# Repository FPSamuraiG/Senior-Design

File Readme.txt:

An Electronic Enrichment System for Saltwater Animal Enclosures

University of Cincinnati
CEAS
EE/ELTN Senior Design
April 2022

Team Members:
  Chris Dombrosky
  Brandon Carroll
  Nathaniel Collum
  Hayden Lampert

Advisors:
  Dr. Dieter Vanderelst
  Dr. Katie Kalafut
  
This repository contains code, PCB files, 3D models, and documentation for this senior design project.

3D Models: Contains 3D models for the project's pushbutton enclosure and wireless charging pad as .step files. Also contains .stl files for 3D printing these components.

Datasheets: Contains manufacturer datasheets for key project components.

PDB Files: Contains EAGLE files for the projects PCBs. Also contains an EAGLE library for custom components used on the PCBs, zipped gerber files for manufacturing additional copies, and component lists for the PCBs.

Release: Contains the .hex file for programming the microcontroller used in this project.

Senior_Design.X: MPLAB X IDE project folder for the microcontroller code. Can be opened as a project in MPLAB X IDE with MPLAB Code Configurator installed.

Project Abstract:

In this project, we designed a prototype input collection system for use in interactive electronic systems in saltwater animal enclosures. Increasing interactivity in enclosures has the potential to improve animal welfare and allow for research and behavior monitoring. Implementing an input device underwater is made difficult by the lack of premade input devices that function underwater, waterproofing requirements, and the ineffectiveness of wireless communication methods underwater. To address these challenges, we designed a prototype input system that includes a custom submersible pushbutton, fiber optic communication, wirelessly rechargeable battery, and extensive waterproofing features. This prototype functions as a pushbutton that can be installed underwater and connected to an Arduino through a fiber optic cable. It provides a tactile input for animals while maintaining safety by not exposing wires or electronics to water. Although it only functions as a pushbutton in its current state, this prototype was designed to be easy to use and easy to add additional sensors or input devices to. Overall, it meets the basic needs presented by our advisors while also making future work and improvements easier.

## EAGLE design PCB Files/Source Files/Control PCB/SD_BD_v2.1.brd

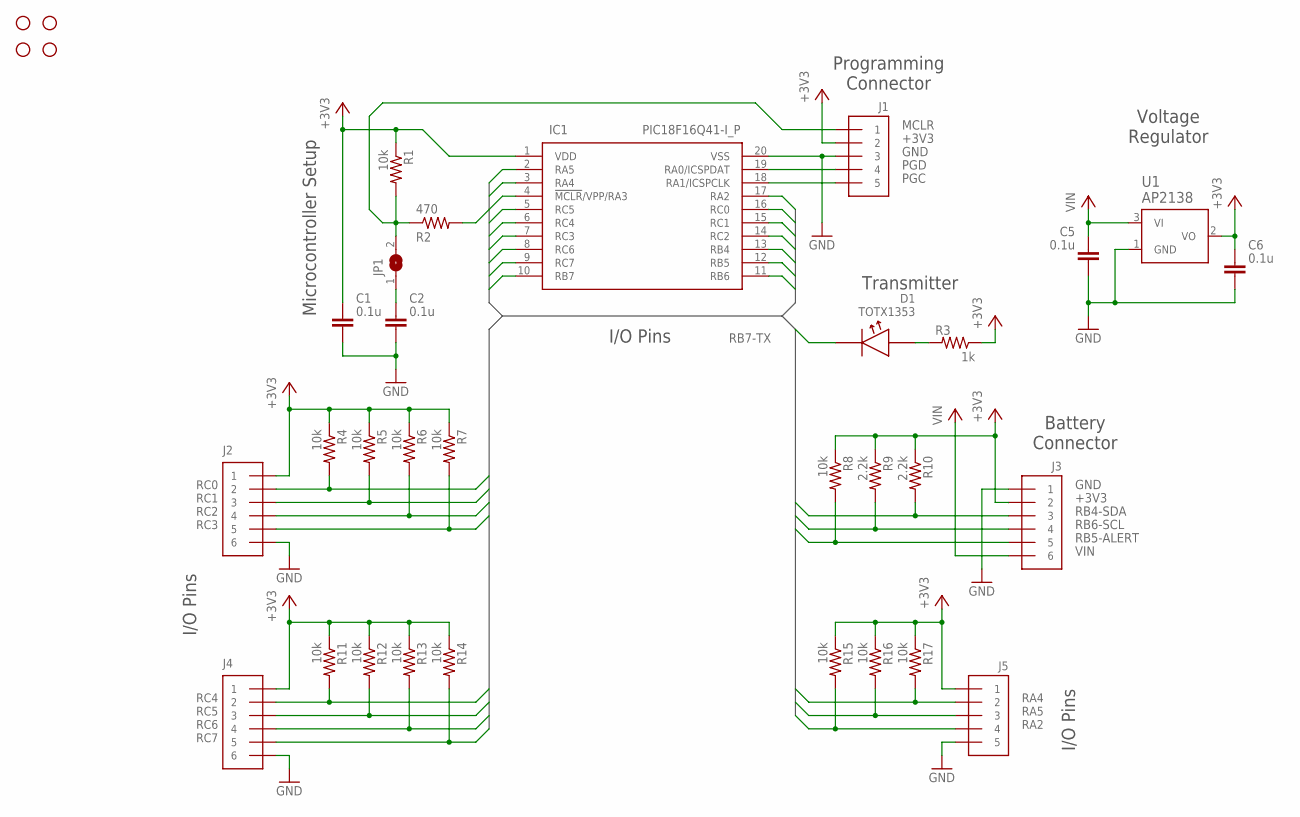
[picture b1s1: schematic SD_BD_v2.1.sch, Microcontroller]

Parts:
C1, C2, C5, C6: 0.1u; CAPC3216X135
D1: TOTX1353; TOXX1353
H1, H2, H3, H4: STAND-OFF
IC1: PIC18F16Q41-I_P; DIP794W56P254L2591H533Q20N
J1: M20-9990546; HDR-5-M
J2, J3, J4: PPTC061LFBN-RC; HDR-6-F
J5: PPTC051LFBN-RC; HDR-5-F
JP1: SJ
R1, R4, R5, R6, R7, R8, R11, R12, R13, R14, R15, R16, R17: 10k; R1206
R2: 470; R1206
R3: 1k; R1206
R9, R10: 2.2k; R1206
U1: AP2138N-3.3TRG1IC3_AP2138N-3.3TRG1_DIO-M; IC3_AP2138N-3.3TRG1_DIO-M

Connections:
+3V3: C1.1, C6.1, IC1.1 (VDD), J1.2, J2.1, J3.2, J4.1, J5.1, R1.1, R3.1, R4.1, R5.1, R6.1, R7.1, R8.1, R9.1, R10.1, R11.1, R12.1, R13.1, R14.1, R15.1, R16.1, R17.1, U1.2 (VO)
GND: C1.2, C2.2, C5.2, C6.2, IC1.20 (VSS), J1.3, J2.6, J3.1, J4.6, J5.5, U1.1 (GND)
MCLR: J1.1, JP1.2, R1.2, R2.1
unnamed: D1.3 (A), R3.2
unnamed: IC1.4 (!MCLR!/VPP/RA3), R2.2
unnamed: C2.1, JP1.1
PGC: IC1.18 (RA1/ICSPCLK), J1.5
PGD: IC1.19 (RA0/ICSPDAT), J1.4
RA2: IC1.17 (RA2), J5.4, R15.2
RA4: IC1.3 (RA4), J5.2, R17.2
RA5: IC1.2 (RA5), J5.3, R16.2
RB4-SDA: IC1.13 (RB4), J3.3, R10.2
RB5-ALERT: IC1.12 (RB5), J3.5, R8.2
RB6-SCL: IC1.11 (RB6), J3.4, R9.2
RB7-TX: D1.2 (K), IC1.10 (RB7)
RC0: IC1.16 (RC0), J2.2, R4.2
RC1: IC1.15 (RC1), J2.3, R5.2
RC2: IC1.14 (RC2), J2.4, R6.2
RC3: IC1.7 (RC3), J2.5, R7.2
RC4: IC1.6 (RC4), J4.2, R11.2
RC5: IC1.5 (RC5), J4.3, R12.2
RC6: IC1.8 (RC6), J4.4, R13.2
RC7: IC1.9 (RC7), J4.5, R14.2
VIN: C5.1, J3.6, U1.3 (VI)

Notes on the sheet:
I/O Pins
Transmitter
Microcontroller Setup
Voltage Regulator
Programming Connector
Battery Connector

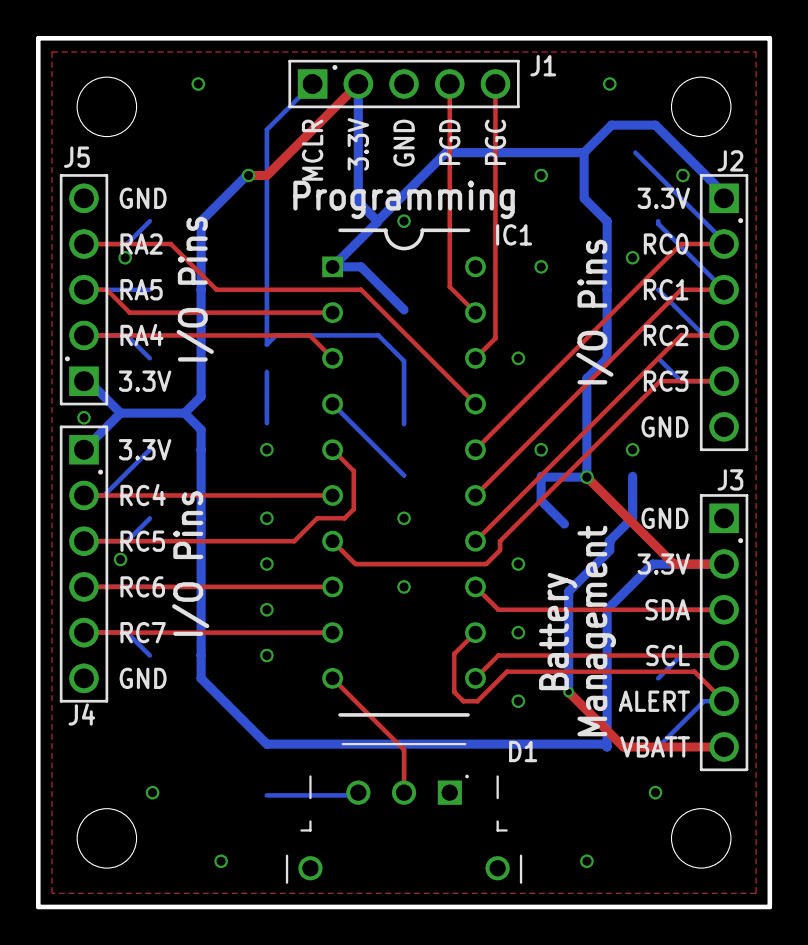
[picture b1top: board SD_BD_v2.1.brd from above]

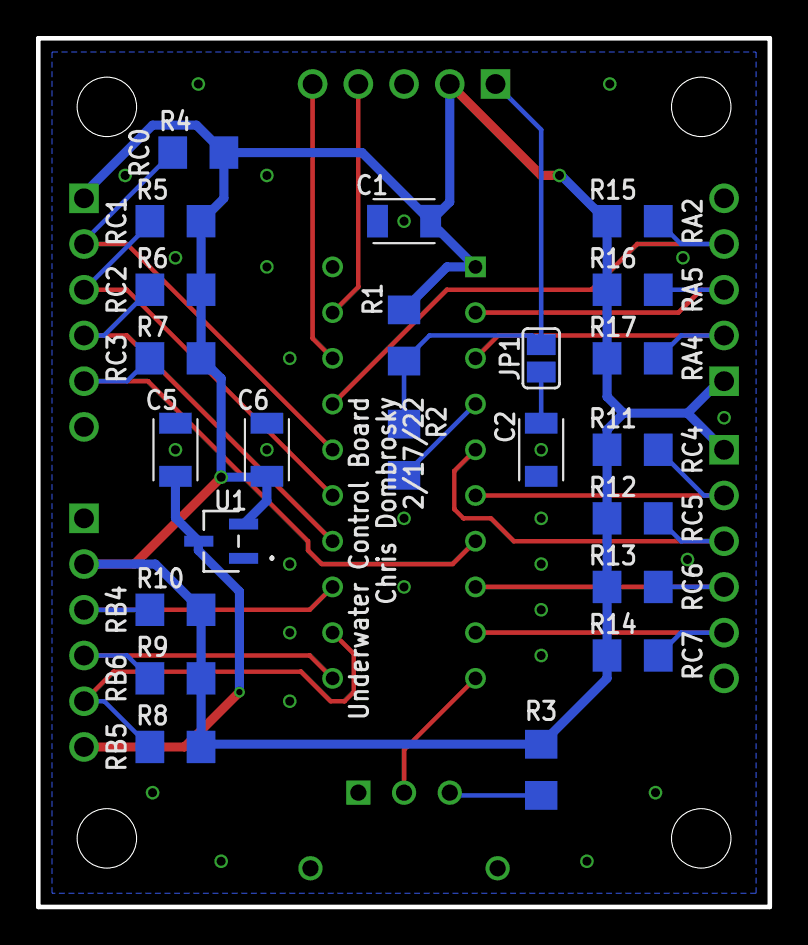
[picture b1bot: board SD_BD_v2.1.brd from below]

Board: 2 copper layers, 40.6 x 48.3 mm, 34 parts (23 on the bottom side), 24 nets.

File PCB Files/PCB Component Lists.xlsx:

Label | Description | Value | Package | Required?
C1 | Microcontroller decoupling capacitor | 0.1uF | 1206 SMD | Required
C2 | MCLR Pin Capacitor (See 4.3 of PIC18F16Q41 Datasheet) | 0.1uF | 1206 SMD | Required
C5 | Voltage regulator decoupling capacitor | 0.1uF | 1206 SMD | Required
C6 | Voltage regulator decoupling capacitor | 0.1uF | 1206 SMD | Required
D1 | Fiber Optic Transmitter (TOTX1350 or equivalent) | n/a | Unique | Required
J1 | Programming connector (0.1" Pitch 5 pin male header) | n/a | 0.1" Pitch TH | Required
J2 | I/O pin connector (0.1" Pitch 6 pin female header) | n/a | 0.1" Pitch TH | Optional
J3 | Battery connector (0.1" Pitch 6 pin female header) | n/a | 0.1" Pitch TH | Optional
J4 | I/O pin connector (0.1" Pitch 6 pin female header) | n/a | 0.1" Pitch TH | Optional
J5 | I/O pin connector (0.1" Pitch 5 pin female header) | n/a | 0.1" Pitch TH | Optional
JP1 | MCLR capacitor solder jumper (See 4.3 of PIC18F16Q41 Datasheet) | n/a | SMD | Required
R1 | MCLR pullup resistor (See 4.3 of PIC18F16Q41 Datasheet) | 10kΩ | 1206 SMD | Required
R2 | MCLR current limiting resistor (See 4.3 of PIC18F16Q41 Datasheet) | 470kΩ | 1206 SMD | Required
R3 | Fiber transmitter curent limiting resistor (See TOTX1353 datasheet) | 1kΩ | 1206 SMD | Required
R4 | I/O optional pullup resistor | 10kΩ | 1206 SMD | Optional
R5 | I/O optional pullup resistor | 10kΩ | 1206 SMD | Optional
R6 | I/O optional pullup resistor | 10kΩ | 1206 SMD | Optional
R7 | I/O optional pullup resistor | 10kΩ | 1206 SMD | Optional
R8 | Fuel gauge alert pullup resistor | 10kΩ | 1206 SMD | Optional
R9 | I2C SCL line pullup resistor | 2.2kΩ | 1206 SMD | Required
R10 | I2C SDA line pullup resistor | 2.2kΩ | 1206 SMD | Required
R11 | I/O optional pullup resistor | 10kΩ | 1206 SMD | Optional
R12 | I/O optional pullup resistor | 10kΩ | 1206 SMD | Optional
R13 | I/O optional pullup resistor | 10kΩ | 1206 SMD | Optional
R14 | I/O optional pullup resistor | 10kΩ | 1206 SMD | Optional
R15 | Reed switch pullup resistor | 10kΩ | 1206 SMD | Required
R16 | I/O optional pullup resistor | 10kΩ | 1206 SMD | Optional
R17 | I/O optional pullup resistor | 10kΩ | 1206 SMD | Optional
IC1 | PIC18F16Q41 microcontroller | n/a | 20 DIP/DIL | Required
U1 | AP2138N-3.3TRG1 linear voltage regulator (3.3V out) | n/a | SOT23-3 | Required

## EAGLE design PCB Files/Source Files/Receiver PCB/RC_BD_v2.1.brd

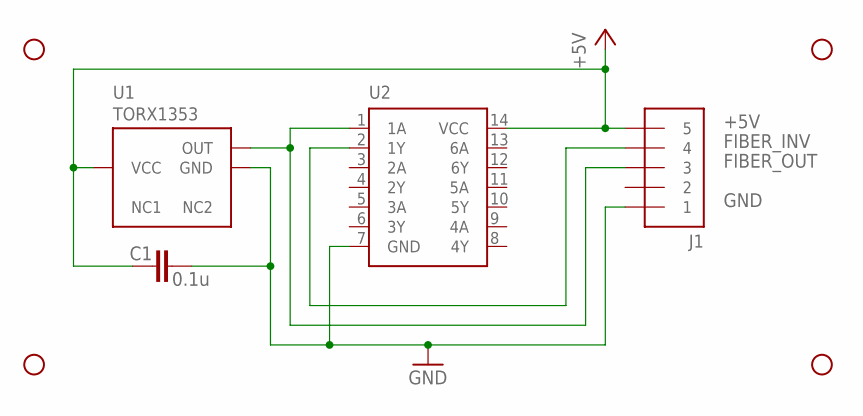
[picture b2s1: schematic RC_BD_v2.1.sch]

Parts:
C1: 0.1u; CAPC3216X135
H1, H2, H3, H4: STAND-OFF
J1: PPTC051LFBN-RC; HDR-5-F
U1: TORX1353; TOXX1353
U2: SN74HC04AN; DIL14

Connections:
+5V: C1.1, J1.5, U1.3 (VCC), U2.14 (VCC)
FIBER_INV: J1.4, U2.2 (1Y)
FIBER_OUT: J1.3, U1.1 (OUT), U2.1 (1A)
GND: C1.2, J1.1, U1.2 (GND), U2.7 (GND)

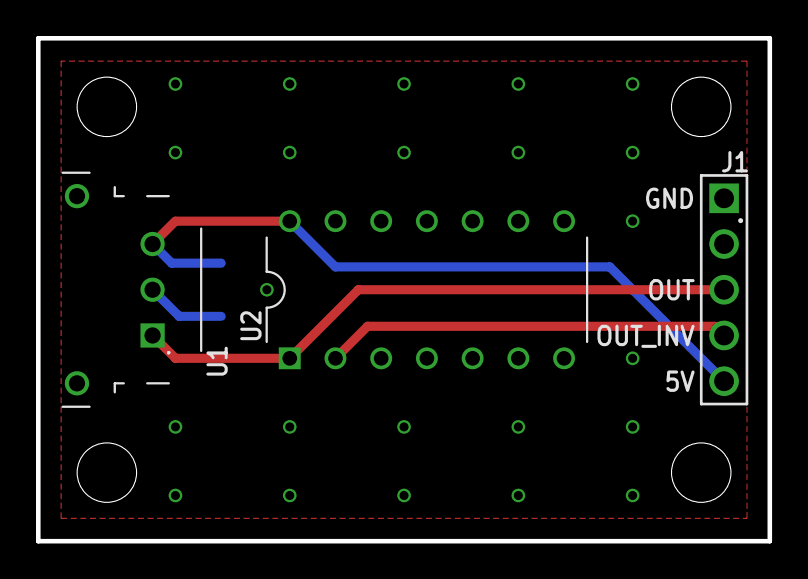
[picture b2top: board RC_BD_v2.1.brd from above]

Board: 2 copper layers, 40.6 x 27.9 mm, 8 parts (1 on the bottom side), 4 nets.

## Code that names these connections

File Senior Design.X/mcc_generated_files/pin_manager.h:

/**
  @Generated Pin Manager Header File

  @Company:
    Microchip Technology Inc.

  @File Name:
    pin_manager.h

  @Summary:
    This is the Pin Manager file generated using PIC10 / PIC12 / PIC16 / PIC18 MCUs

  @Description
    This header file provides APIs for driver for .
    Generation Information :
        Product Revision  :  PIC10 / PIC12 / PIC16 / PIC18 MCUs - 1.81.7
        Device            :  PIC18F16Q41
        Driver Version    :  2.11
    The generated drivers are tested against the following:
        Compiler          :  XC8 2.31 and above
        MPLAB 	          :  MPLAB X 5.45	
*/

/*
    (c) 2018 Microchip Technology Inc. and its subsidiaries. 
    
    Subject to your compliance with these terms, you may use Microchip software and any 
    derivatives exclusively with Microchip products. It is your responsibility to comply with third party 
    license terms applicable to your use of third party software (including open source software) that 
    may accompany Microchip software.
    
    THIS SOFTWARE IS SUPPLIED BY MICROCHIP "AS IS". NO WARRANTIES, WHETHER 
    EXPRESS, IMPLIED OR STATUTORY, APPLY TO THIS SOFTWARE, INCLUDING ANY 
    IMPLIED WARRANTIES OF NON-INFRINGEMENT, MERCHANTABILITY, AND FITNESS 
    FOR A PARTICULAR PURPOSE.
    
    IN NO EVENT WILL MICROCHIP BE LIABLE FOR ANY INDIRECT, SPECIAL, PUNITIVE, 
    INCIDENTAL OR CONSEQUENTIAL LOSS, DAMAGE, COST OR EXPENSE OF ANY KIND 
    WHATSOEVER RELATED TO THE SOFTWARE, HOWEVER CAUSED, EVEN IF MICROCHIP 
    HAS BEEN ADVISED OF THE POSSIBILITY OR THE DAMAGES ARE FORESEEABLE. TO 
    THE FULLEST EXTENT ALLOWED BY LAW, MICROCHIP'S TOTAL LIABILITY ON ALL 
    CLAIMS IN ANY WAY RELATED TO THIS SOFTWARE WILL NOT EXCEED THE AMOUNT 
    OF FEES, IF ANY, THAT YOU HAVE PAID DIRECTLY TO MICROCHIP FOR THIS 
    SOFTWARE.
*/

#ifndef PIN_MANAGER_H
#define PIN_MANAGER_H

/**
  Section: Included Files
*/

#include <xc.h>

#define INPUT   1
#define OUTPUT  0

#define HIGH    1
#define LOW     0

#define ANALOG      1
#define DIGITAL     0

#define PULL_UP_ENABLED      1
#define PULL_UP_DISABLED     0

// get/set RA2 procedures
#define RA2_SetHigh()            do { LATAbits.LATA2 = 1; } while(0)
#define RA2_SetLow()             do { LATAbits.LATA2 = 0; } while(0)
#define RA2_Toggle()             do { LATAbits.LATA2 = ~LATAbits.LATA2; } while(0)
#define RA2_GetValue()              PORTAbits.RA2
#define RA2_SetDigitalInput()    do { TRISAbits.TRISA2 = 1; } while(0)
#define RA2_SetDigitalOutput()   do { TRISAbits.TRISA2 = 0; } while(0)
#define RA2_SetPullup()             do { WPUAbits.WPUA2 = 1; } while(0)
#define RA2_ResetPullup()           do { WPUAbits.WPUA2 = 0; } while(0)
#define RA2_SetAnalogMode()         do { ANSELAbits.ANSELA2 = 1; } while(0)
#define RA2_SetDigitalMode()        do { ANSELAbits.ANSELA2 = 0; } while(0)

// get/set RB4 procedures
#define RB4_SetHigh()            do { LATBbits.LATB4 = 1; } while(0)
#define RB4_SetLow()             do { LATBbits.LATB4 = 0; } while(0)
#define RB4_Toggle()             do { LATBbits.LATB4 = ~LATBbits.LATB4; } while(0)
#define RB4_GetValue()              PORTBbits.RB4
#define RB4_SetDigitalInput()    do { TRISBbits.TRISB4 = 1; } while(0)
#define RB4_SetDigitalOutput()   do { TRISBbits.TRISB4 = 0; } while(0)
#define RB4_SetPullup()             do { WPUBbits.WPUB4 = 1; } while(0)
#define RB4_ResetPullup()           do { WPUBbits.WPUB4 = 0; } while(0)
#define RB4_SetAnalogMode()         do { ANSELBbits.ANSELB4 = 1; } while(0)
#define RB4_SetDigitalMode()        do { ANSELBbits.ANSELB4 = 0; } while(0)

// get/set RB5 procedures
#define RB5_SetHigh()            do { LATBbits.LATB5 = 1; } while(0)
#define RB5_SetLow()             do { LATBbits.LATB5 = 0; } while(0)
#define RB5_Toggle()             do { LATBbits.LATB5 = ~LATBbits.LATB5; } while(0)
#define RB5_GetValue()              PORTBbits.RB5
#define RB5_SetDigitalInput()    do { TRISBbits.TRISB5 = 1; } while(0)
#define RB5_SetDigitalOutput()   do { TRISBbits.TRISB5 = 0; } while(0)
#define RB5_SetPullup()             do { WPUBbits.WPUB5 = 1; } while(0)
#define RB5_ResetPullup()           do { WPUBbits.WPUB5 = 0; } while(0)
#define RB5_SetAnalogMode()         do { ANSELBbits.ANSELB5 = 1; } while(0)
#define RB5_SetDigitalMode()        do { ANSELBbits.ANSELB5 = 0; } while(0)

// get/set RB6 procedures
#define RB6_SetHigh()            do { LATBbits.LATB6 = 1; } while(0)
#define RB6_SetLow()             do { LATBbits.LATB6 = 0; } while(0)
#define RB6_Toggle()             do { LATBbits.LATB6 = ~LATBbits.LATB6; } while(0)
#define RB6_GetValue()              PORTBbits.RB6
#define RB6_SetDigitalInput()    do { TRISBbits.TRISB6 = 1; } while(0)
#define RB6_SetDigitalOutput()   do { TRISBbits.TRISB6 = 0; } while(0)
#define RB6_SetPullup()             do { WPUBbits.WPUB6 = 1; } while(0)
#define RB6_ResetPullup()           do { WPUBbits.WPUB6 = 0; } while(0)
#define RB6_SetAnalogMode()         do { ANSELBbits.ANSELB6 = 1; } while(0)
#define RB6_SetDigitalMode()        do { ANSELBbits.ANSELB6 = 0; } while(0)

// get/set RB7 procedures
#define RB7_SetHigh()            do { LATBbits.LATB7 = 1; } while(0)
#define RB7_SetLow()             do { LATBbits.LATB7 = 0; } while(0)
#define RB7_Toggle()             do { LATBbits.LATB7 = ~LATBbits.LATB7; } while(0)
#define RB7_GetValue()              PORTBbits.RB7
#define RB7_SetDigitalInput()    do { TRISBbits.TRISB7 = 1; } while(0)
#define RB7_SetDigitalOutput()   do { TRISBbits.TRISB7 = 0; } while(0)
#define RB7_SetPullup()             do { WPUBbits.WPUB7 = 1; } while(0)
#define RB7_ResetPullup()           do { WPUBbits.WPUB7 = 0; } while(0)
#define RB7_SetAnalogMode()         do { ANSELBbits.ANSELB7 = 1; } while(0)
#define RB7_SetDigitalMode()        do { ANSELBbits.ANSELB7 = 0; } while(0)

// get/set RC7 procedures
#define RC7_SetHigh()            do { LATCbits.LATC7 = 1; } while(0)
#define RC7_SetLow()             do { LATCbits.LATC7 = 0; } while(0)
#define RC7_Toggle()             do { LATCbits.LATC7 = ~LATCbits.LATC7; } while(0)
#define RC7_GetValue()              PORTCbits.RC7
#define RC7_SetDigitalInput()    do { TRISCbits.TRISC7 = 1; } while(0)
#define RC7_SetDigitalOutput()   do { TRISCbits.TRISC7 = 0; } while(0)
#define RC7_SetPullup()             do { WPUCbits.WPUC7 = 1; } while(0)
#define RC7_ResetPullup()           do { WPUCbits.WPUC7 = 0; } while(0)
#define RC7_SetAnalogMode()         do { ANSELCbits.ANSELC7 = 1; } while(0)
#define RC7_SetDigitalMode()        do { ANSELCbits.ANSELC7 = 0; } while(0)

/**
   @Param
    none
   @Returns
    none
   @Description
    GPIO and peripheral I/O initialization
   @Example
    PIN_MANAGER_Initialize();
 */
void PIN_MANAGER_Initialize (void);

/**
 * @Param
    none
 * @Returns
    none
 * @Description
    Interrupt on Change Handling routine
 * @Example
    PIN_MANAGER_IOC();
 */
void PIN_MANAGER_IOC(void);



#endif // PIN_MANAGER_H
/**
 End of File
*/

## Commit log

2022-01-20 Added Readme file.
2022-01-24 Adjusted some device and peripheral settings in MCC. Added source/header files for uart functions. Added a function to send a string over UART. Added a call to this function to main to use in testing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
2022-01-26 Updated code for test purposes. Modified main loop to turn on the built in LED on the dev board when the button is pressed.
2022-01-27 Renamed project folder to remove space.
2022-01-27 Delete Senior Design.X directory
    Removed old directory with space in name.
2022-01-31 Added file for sleep mode related functions. Added second button to main loop for putting MCU into and out of sleep. Added interrupt on change to this button to send "BTN1" over UART when it is drive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
2022-02-01 Updated main loop and configuration settings to get sleep mode to work.
2022-02-02 Added .gitignore file
2022-02-02 Updated main loop.
2022-02-02 Removed ignored files from git
2022-02-03 Added <cr><lf> to all output strings. Improved startup message.
2022-02-09 Updated main loop to generate battery status messages based on charge level. Added source and header files for battery related functions
2022-02-09 Removing unecessary files
2022-02-14 More updates
2022-02-20 Made sure transmit buffer is not full before writing new characters when transmitting a string. Fixed source/header file designations for created files.
2022-02-22 Removed unnecessary i/o pins and uninverted uart polarity
2022-02-22 Added weak pull ups
2022-02-24 Added debounce to button interrupt.
2022-03-01 Removed weak pull ups (PCB will have external pullups) Removed newline characters from output strings. (End of message is indicated by carriage return \r)
2022-03-01 Changed button input from pin RC0 to RA2 as this is where the reed switch will be connected on the PCB.
2022-03-03 Added message for button release.
2022-03-06 Changed code so messages are only sent from the main loop in order to prevent the button interrupt from sending a message in the middle of the battery message.
    Added debouncing checks to main loop.
2022-03-07 Added alternate method for input debounce and handling (commented out)
2022-03-07 Cleaned up and added comments to new debounce code.
2022-03-21 Slight changes to debounce behavior to not miss the button being released.
2022-03-23 Discovered that if the button is pressed and released quickly enough, the state change upon release will happen when the interrupt from the state change upon being pressed is being processed. This ca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
    Solution: Added a 1 second timer after entering sleep mode while the button is pressed. This timer triggers an interrupt that records the state of the button and halts the timer. This also wakes the 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
2022-03-23 Discovered that if the button is pressed and released quickly enough, the state change upon release will happen when the interrupt from the state change upon being pressed is being processed. This ca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
    Solution: Added a 1 second timer after entering sleep mode while the button is pressed. This timer triggers an interrupt that records the state of the button and halts the timer. This also wakes the 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
2022-04-05 Added fuel gauge functions
2022-04-14 Initial Commit of source and stl files for 3D printed components.
2022-04-14 Initial commit of source and gerber files for PCBs.
2022-04-18 Changed table theme to dark grey.
2022-04-21 Replaced incorrect stl file with correct file.
2022-04-24 Added additional folders

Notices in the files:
parts and their libraries:
SparkFun-Hardware: Licensing: Creative Commons ShareAlike 4.0 International - https://creativecommons.org/licenses/by-sa/4.0
COPYRIGHT: Copyright (C) 2022 Ultra Librarian. All rights reserved.
